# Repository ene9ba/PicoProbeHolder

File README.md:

# Pico Probe Adapter

Debuging the Raspberry Pi Pico by using the Pico as a Probe is a great thing, but by using a breadborard as interface to the
target is a little bit anoying. So I decided to design a PICO Probe pcb to make it easier to debug software without any contact 
and connection problems. A Resetbutton, as well as two jumpers to supply the target with 3.3V or 5V are integrated.

**Version 1.1 :**  optimized ground level, case design added

License

Creative Commons License
This work is licensed under a Creative Commons Attribution-NonCommercial-ShareAlike 4.0 International License.

Feel free to use the design in your private/educational projects, but don't try to sell the design or products based on it without getting my consent first. The idea here is to share knowledge, not to enable others to simply sell my work. Thank you for understanding.

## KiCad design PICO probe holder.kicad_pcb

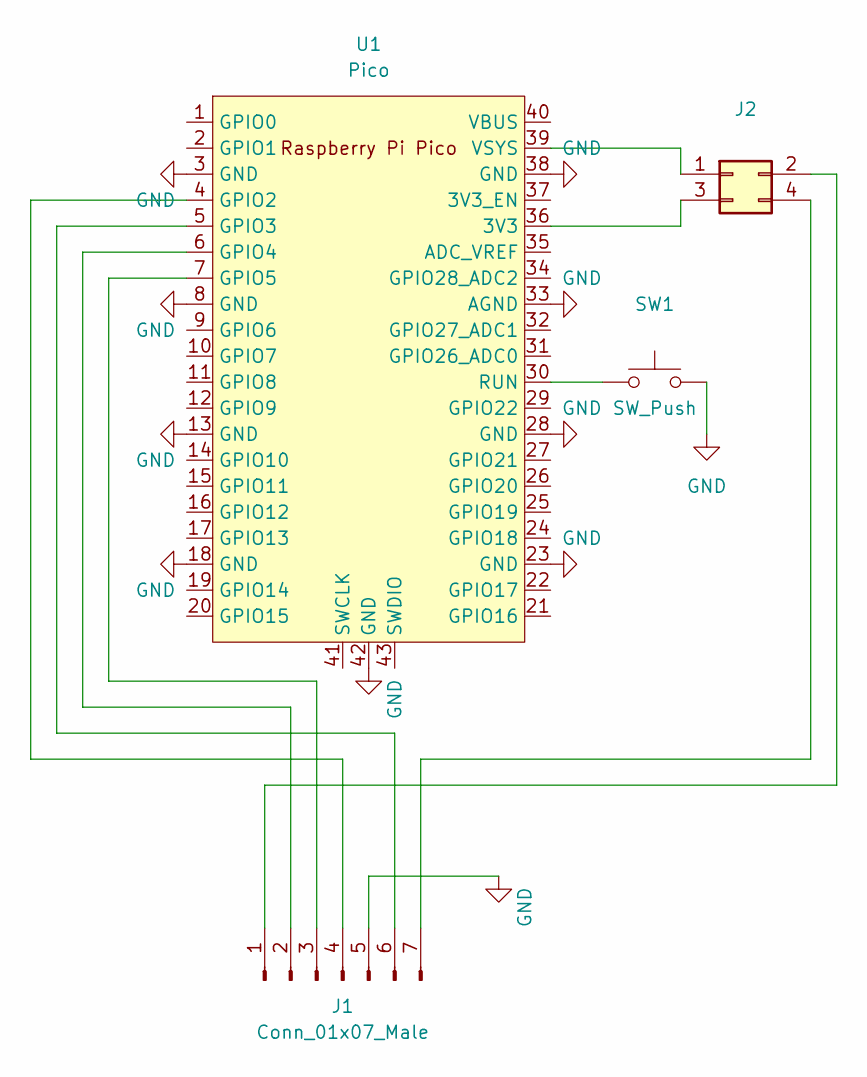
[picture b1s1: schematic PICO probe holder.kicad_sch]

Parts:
J1: Conn_01x07_Male; JST_XH_B7B-XH-A_1x07_P2.50mm_Vertical
J2: Conn_02x02_Odd_Even; PinHeader_2x02_P2.54mm_Vertical
SW1: SW_Push; SW_PUSH_6mm
U1: Pico; RPi_Pico_SMD_TH

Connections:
GND: J1.5, SW1.2, U1.3 (GND), U1.8 (GND), U1.13 (GND), U1.18 (GND), U1.23 (GND), U1.28 (GND), U1.33 (AGND), U1.38 (GND), U1.42 (GND)
unnamed: J1.1, J2.2
unnamed: J1.2, U1.6 (GPIO4)
unnamed: J1.3, U1.7 (GPIO5)
unnamed: J1.4, U1.4 (GPIO2)
unnamed: J1.6, U1.5 (GPIO3)
unnamed: J1.7, J2.4
unnamed: J2.1, U1.39 (VSYS)
unnamed: J2.3, U1.36 (3V3)
unnamed: SW1.1, U1.30 (RUN)

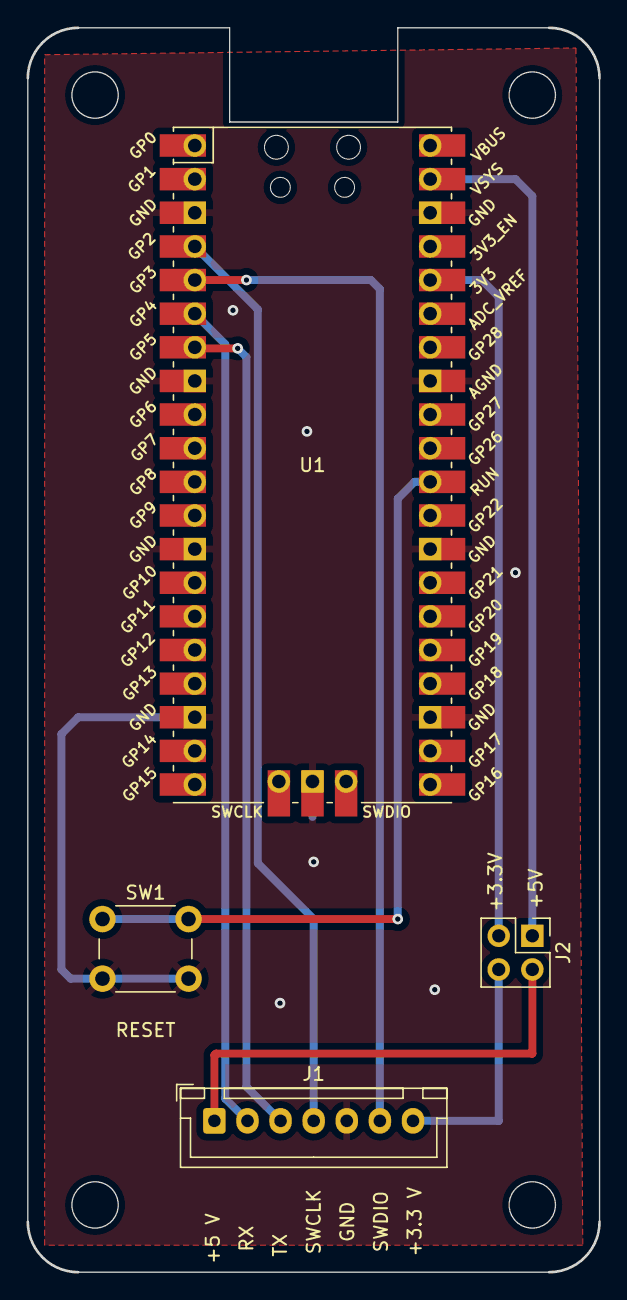
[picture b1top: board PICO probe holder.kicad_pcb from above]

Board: 2 copper layers, 43.2 x 94.0 mm, 4 parts (0 on the bottom side), 10 nets.

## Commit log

2022-04-18 inital commit
2022-06-13 optimized ground Layer, case design added V1.1

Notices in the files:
PICO probe holder.kicad_pcb:
License CC BY-NC-SA 4.0
